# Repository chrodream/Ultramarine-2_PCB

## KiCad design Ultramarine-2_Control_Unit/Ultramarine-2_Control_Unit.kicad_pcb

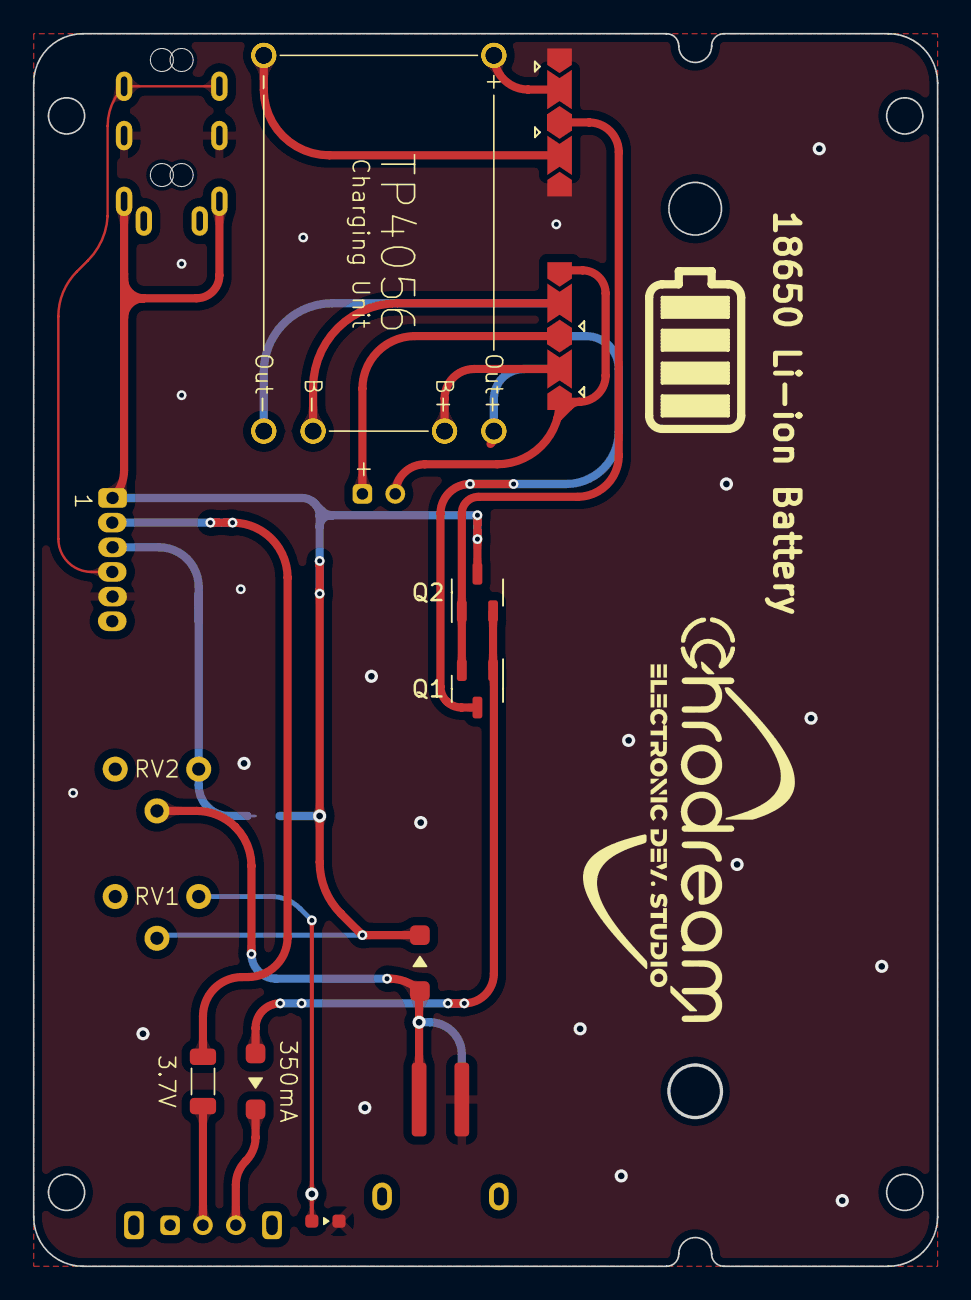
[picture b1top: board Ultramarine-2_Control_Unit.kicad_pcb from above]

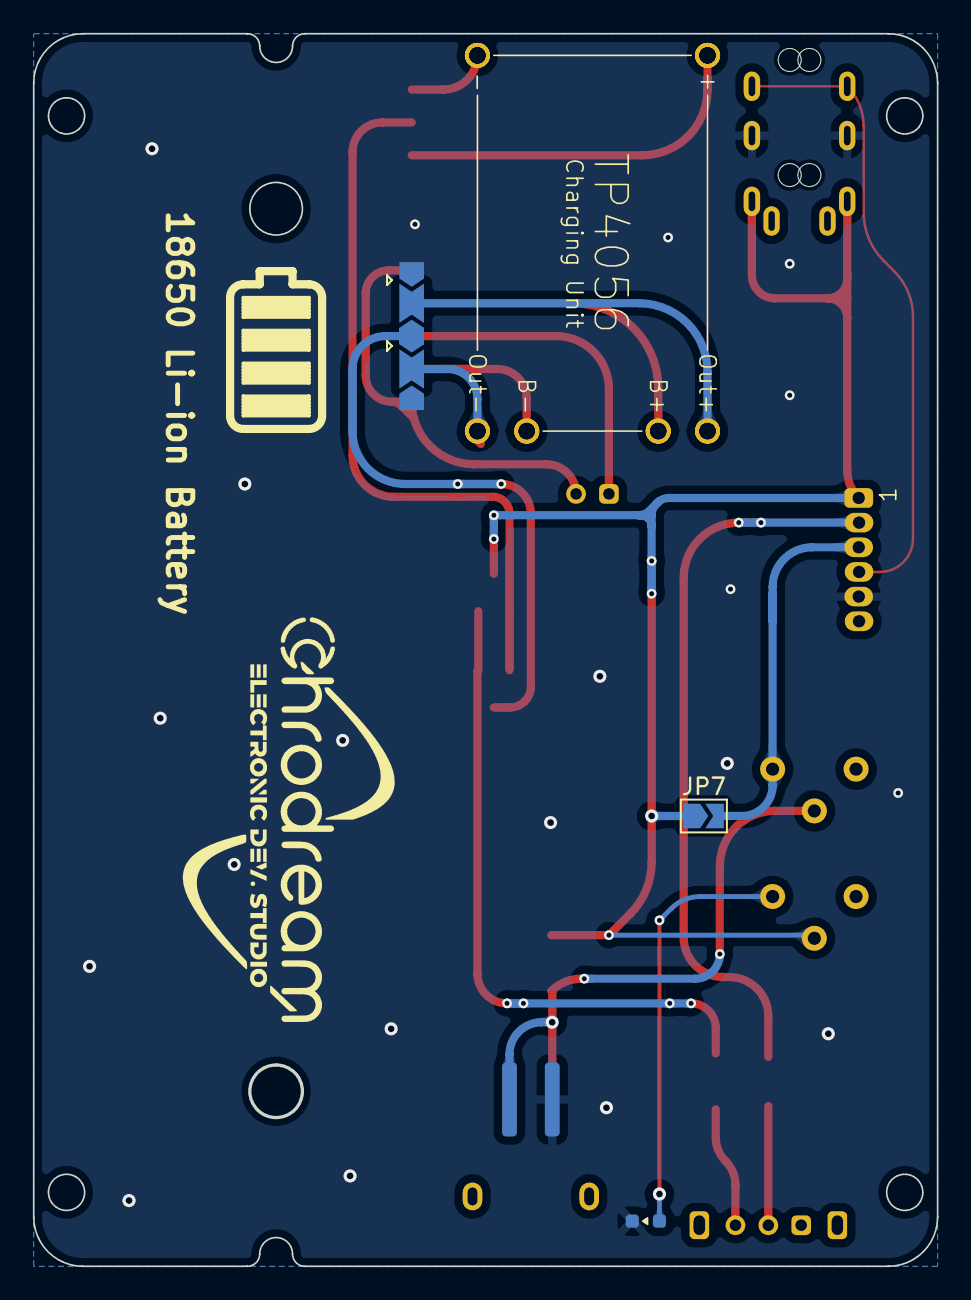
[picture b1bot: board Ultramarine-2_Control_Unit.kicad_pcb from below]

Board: 2 copper layers, 54.9 x 74.9 mm, 22 parts (4 on the bottom side), 20 nets.

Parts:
BT1: LiPo/18650; Battery
BT2: Qi Charging Unit; Micro_USB_Charging
D1: -0.7V; SOD-123
D2: D; SOD-123
D3: Power (WH); LED1608
F1: 350mA; MF-NSMF
J1: Generic_connector; JST_ZH_6
J2: TRRS; MJ-4PP-9
JP1: OUT+ Jumper; Jumper 3pin
JP2: IN+ Jumper; Jumper 3pin
JP3, JP4, JP5, JP6: Jumper 3pin
JP7: Enable_battery_less_mode; SolderJumper-2_P1.3mm_Open_TrianglePad1.0x1.5mm
Q1, Q2: SSM3J332R; SOT-23-3
RV1, RV2: 10K; R_variable
SW1: Slide; SK-12D11VG3
U1, U2: TP4056

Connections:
+5V: D2.1 (K), J1.1, J2.2, JP7.1 (A), Q2.3 (S), RV1.2
/B+: BT1.1 (+), JP1.3 (B), JP3.1 (A)
/B-: BT1.2 (-), JP1.1 (A), JP3.3 (B)
/Bat+: F1.2, J1.2
/Charging: BT2.1 (+), D2.2 (A), RV2.2
/FlexLED: J1.3, JP7.2 (B), RV2.3
/IN+: JP2.3 (B), JP5.1 (A), Q1.2 (G), Q2.1 (D)
/OUT+: JP4.3 (B), JP6.1 (A), Q1.3 (S)
/data: J1.4, J2.4
GND: BT2.2 (-), D3.1 (K), J1.5, J2.3, JP2.1 (A), JP4.1 (A), JP5.3 (B), JP6.3 (B)
unnamed: D1.2 (A), Q1.1 (D), Q2.2 (G)
unnamed: D1.1 (K), SW1.3 (C)
unnamed: D3.2 (A), RV1.3
unnamed: JP1.2 (C), U1.4 (B+), U2.5 (B-)
unnamed: JP2.2 (C), U1.1 (+), U2.2 (-)
unnamed: JP3.2 (C), U1.5 (B-), U2.4 (B+)
unnamed: JP4.2 (C), U1.6 (Out-), U2.3 (Out+)
unnamed: JP5.2 (C), U1.2 (-), U2.1 (+)
unnamed: JP6.2 (C), U1.3 (Out+), U2.6 (Out-)
unnamed: F1.1, SW1.2 (B)

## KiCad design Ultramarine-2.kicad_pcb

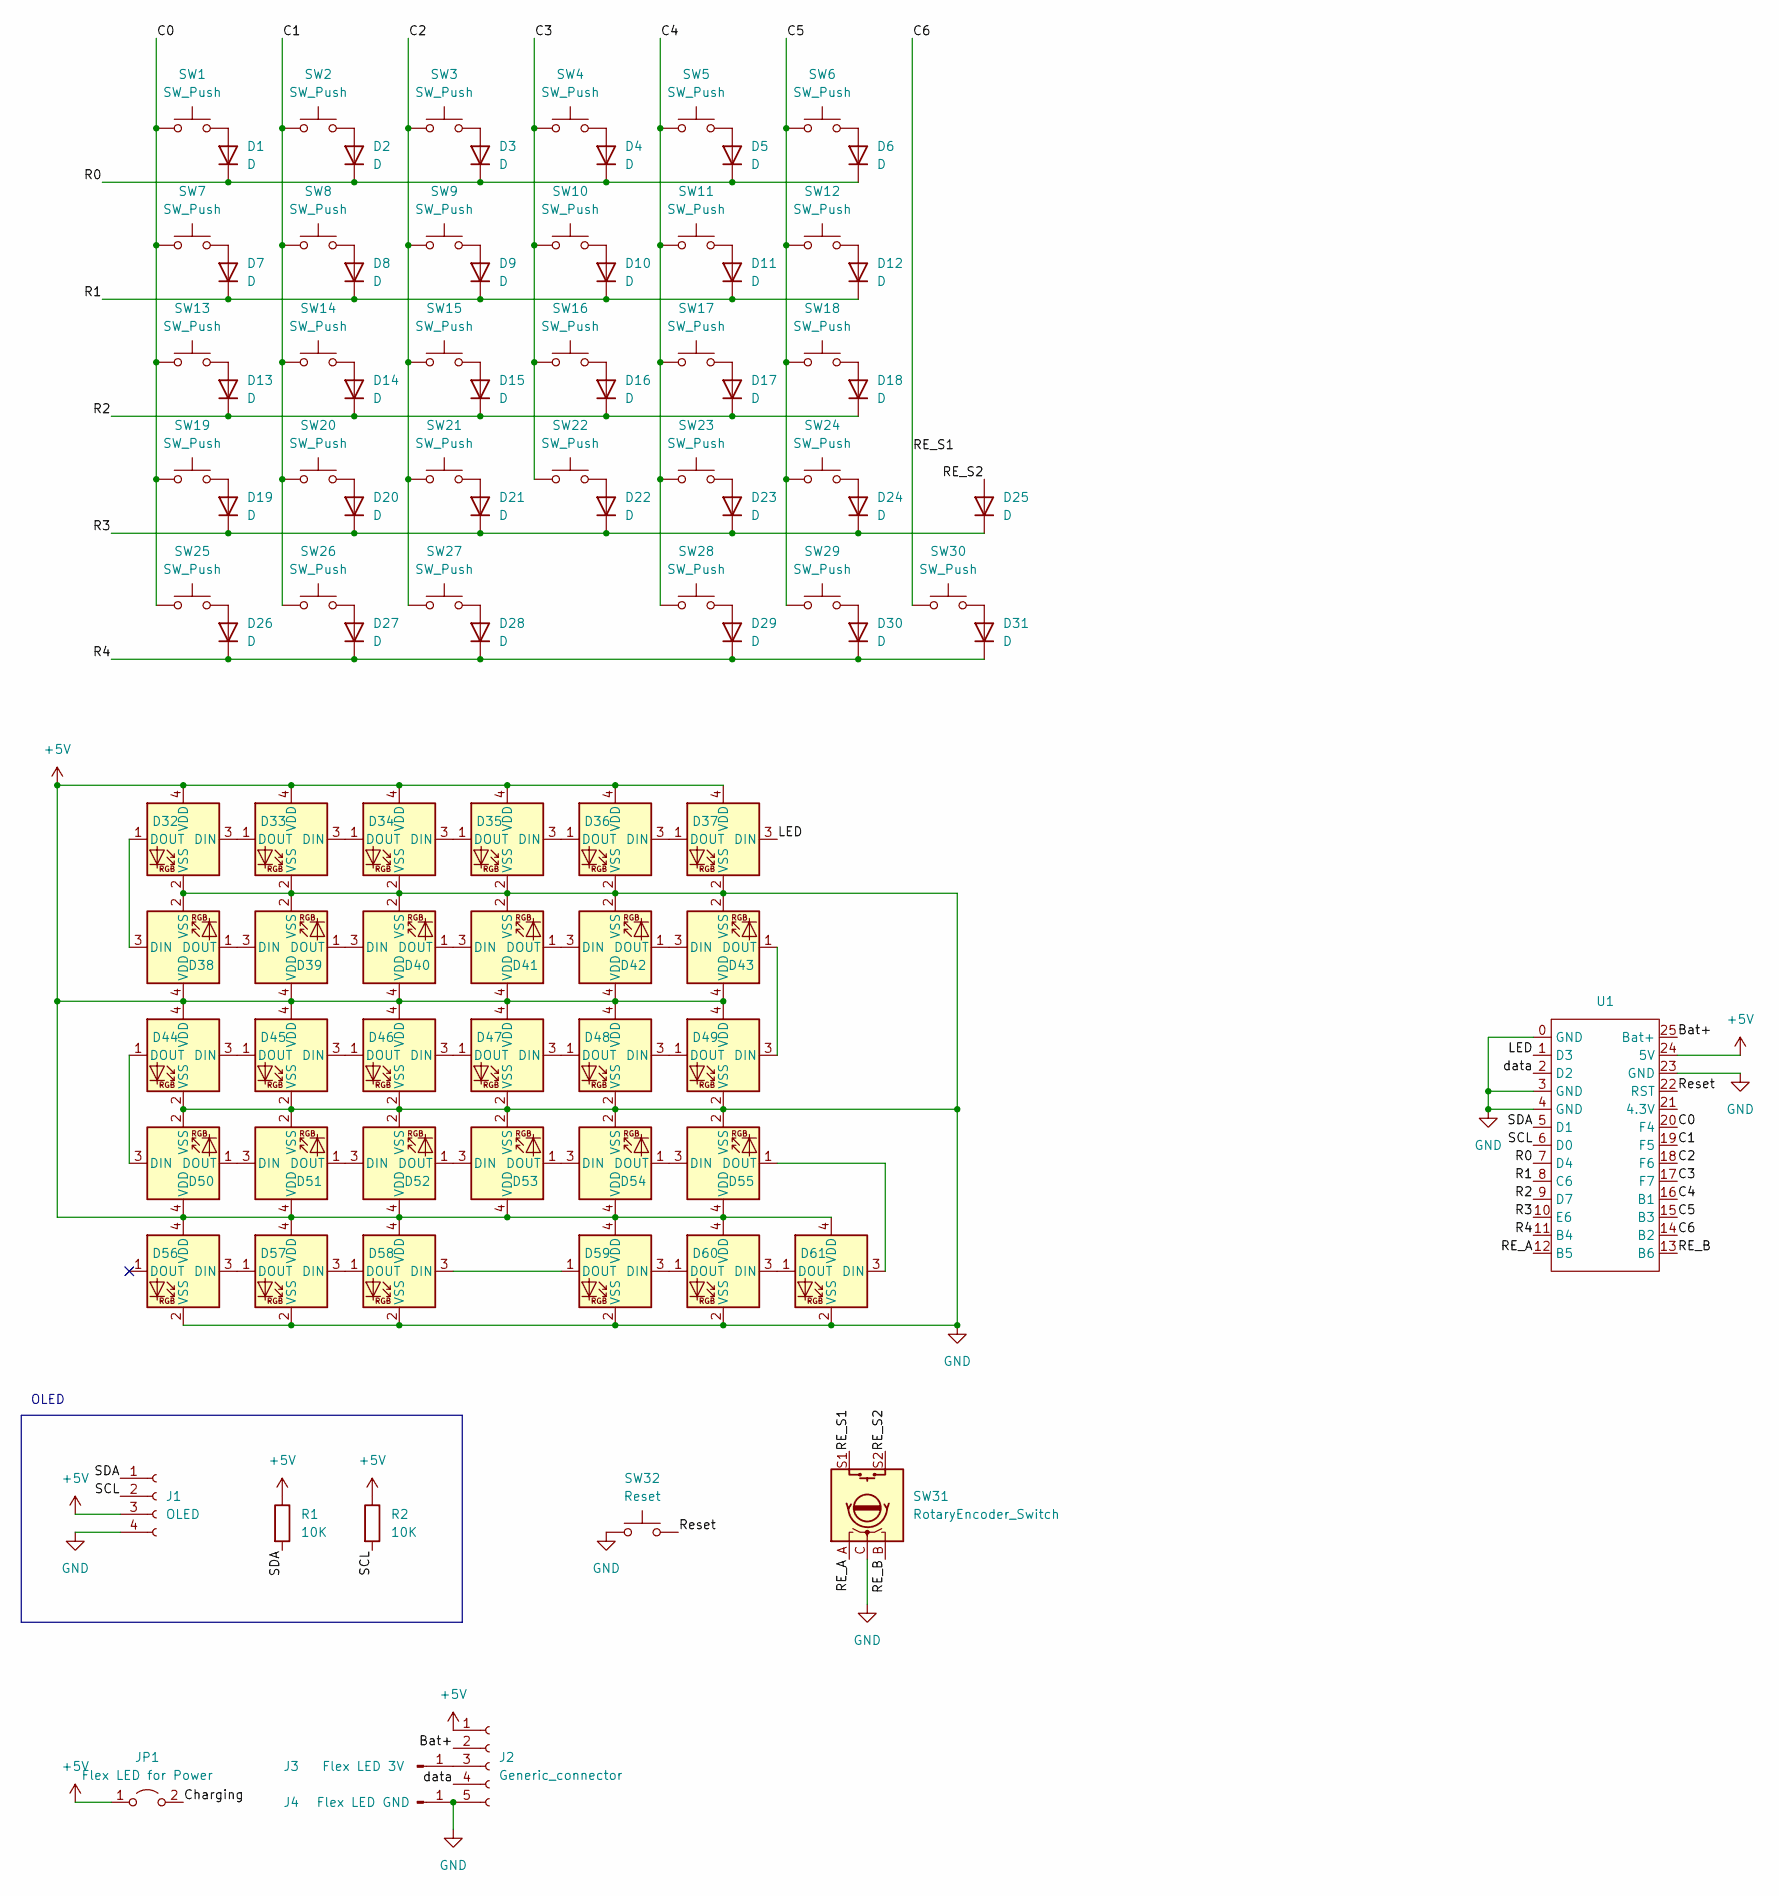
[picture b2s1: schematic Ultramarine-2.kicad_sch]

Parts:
D1, D2, D3, D4, D5, D6, D7, D8, D9, D10, D11, D12, D13, D14, D15, D16, D17, D18, D19, D20, D21, D22, D23, D24, D25, D26, D27, D28, D29, D30, D31: D; SOD-123
D32, D33, D34, D35, D36, D37, D38, D39, D40, D41, D42, D43, D44, D45, D46, D47, D48, D49, D50, D51, D52, D53, D54, D55, D56, D57, D58, D59, D60, D61: SK6812MINI; SK6812-mini
J1: OLED
J2: Generic_connector; PinHeader_1x05_P2.54mm_Horizontal
J3: Flex LED 3V; PTH_Flex_LED
J4: Flex LED GND; PTH_Flex_LED
JP1: Flex LED for Power; SolderJumper-2_P1.3mm_Open_TrianglePad1.0x1.5mm
R1, R2: 10K; R_0603_1608Metric
SW1, SW2, SW3, SW4, SW5, SW6, SW7, SW8, SW9, SW10, SW11, SW12, SW13, SW14, SW15, SW16, SW17, SW18, SW19, SW20, SW21, SW22, SW23, SW24, SW25, SW26, SW27, SW28, SW29, SW30: SW_Push; MX-hotswap
SW31: RotaryEncoder_Switch; EC12
SW32: Reset; Tactlie_Switch
U1: BLE Micro Pro

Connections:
+5V: D32.4 (VDD), D33.4 (VDD), D34.4 (VDD), D35.4 (VDD), D36.4 (VDD), D37.4 (VDD), D38.4 (VDD), D39.4 (VDD), D40.4 (VDD), D41.4 (VDD), D42.4 (VDD), D43.4 (VDD), D44.4 (VDD), D45.4 (VDD), D46.4 (VDD), D47.4 (VDD), D48.4 (VDD), D49.4 (VDD), D50.4 (VDD), D51.4 (VDD), D52.4 (VDD), D53.4 (VDD), D54.4 (VDD), D55.4 (VDD), D56.4 (VDD), D57.4 (VDD), D58.4 (VDD), D59.4 (VDD), D60.4 (VDD), D61.4 (VDD), J1.3, J2.1, JP1.1 (A), R1.1, R2.1, U1.24 (5V)
/Bat+: J2.2, U1.25 (Bat+)
/C0: SW1.2, SW7.2, SW13.2, SW19.2, SW25.2, U1.20 (F4)
/C1: SW2.2, SW8.2, SW14.2, SW20.2, SW26.2, U1.19 (F5)
/C2: SW3.2, SW9.2, SW15.2, SW21.2, SW27.2, U1.18 (F6)
/C3: SW4.2, SW10.2, SW16.2, SW22.2, U1.17 (F7)
/C4: SW5.2, SW11.2, SW17.2, SW23.2, SW28.1, U1.16 (B1)
/C5: SW6.2, SW12.2, SW18.2, SW24.2, SW29.1, U1.15 (B3)
/C6: SW30.1, SW31.S1, U1.14 (B2)
/Charging: JP1.2 (B)
/LED: D37.3 (DIN), U1.1 (D3)
/R0: D1.1 (K), D2.1 (K), D3.1 (K), D4.1 (K), D5.1 (K), D6.1 (K), U1.7 (D4)
/R1: D7.1 (K), D8.1 (K), D9.1 (K), D10.1 (K), D11.1 (K), D12.1 (K), U1.8 (C6)
/R2: D13.1 (K), D14.1 (K), D15.1 (K), D16.1 (K), D17.1 (K), D18.1 (K), U1.9 (D7)
/R3: D19.1 (K), D20.1 (K), D21.1 (K), D22.1 (K), D23.1 (K), D24.1 (K), D25.1 (K), U1.10 (E6)
/R4: D26.1 (K), D27.1 (K), D28.1 (K), D29.1 (K), D30.1 (K), D31.1 (K), U1.11 (B4)
/RE_A: SW31.A, U1.12 (B5)
/RE_B: SW31.B, U1.13 (B6)
/RE_S2: D25.2 (A), SW31.S2
/Reset: SW32.2, U1.22 (RST)
/SCL: J1.2, R2.2, U1.6 (D0)
/SDA: J1.1, R1.2, U1.5 (D1)
/data: J2.4, U1.2 (D2)
GND: D32.2 (VSS), D33.2 (VSS), D34.2 (VSS), D35.2 (VSS), D36.2 (VSS), D37.2 (VSS), D38.2 (VSS), D39.2 (VSS), D40.2 (VSS), D41.2 (VSS), D42.2 (VSS), D43.2 (VSS), D44.2 (VSS), D45.2 (VSS), D46.2 (VSS), D47.2 (VSS), D48.2 (VSS), D49.2 (VSS), D50.2 (VSS), D51.2 (VSS), D52.2 (VSS), D53.2 (VSS), D54.2 (VSS), D55.2 (VSS), D56.2 (VSS), D57.2 (VSS), D58.2 (VSS), D59.2 (VSS), D60.2 (VSS), D61.2 (VSS), J1.4, J2.5, J4.1, SW31.C, SW32.1, U1.0 (GND), U1.3 (GND), U1.4 (GND), U1.23 (GND)
unnamed: D1.2 (A), SW1.1
unnamed: D2.2 (A), SW2.1
unnamed: D3.2 (A), SW3.1
unnamed: D4.2 (A), SW4.1
unnamed: D5.2 (A), SW5.1
unnamed: D6.2 (A), SW6.1
unnamed: D7.2 (A), SW7.1
unnamed: D8.2 (A), SW8.1
unnamed: D9.2 (A), SW9.1
unnamed: D10.2 (A), SW10.1
unnamed: D11.2 (A), SW11.1
unnamed: D12.2 (A), SW12.1
unnamed: D13.2 (A), SW13.1
unnamed: D14.2 (A), SW14.1
unnamed: D15.2 (A), SW15.1
unnamed: D16.2 (A), SW16.1
unnamed: D17.2 (A), SW17.1
unnamed: D18.2 (A), SW18.1
unnamed: D19.2 (A), SW19.1
unnamed: D20.2 (A), SW20.1
unnamed: D21.2 (A), SW21.1
unnamed: D22.2 (A), SW22.1
unnamed: D23.2 (A), SW23.1
unnamed: D24.2 (A), SW24.1
unnamed: D26.2 (A), SW25.1
unnamed: D27.2 (A), SW26.1
unnamed: D28.2 (A), SW27.1
unnamed: D29.2 (A), SW28.2
unnamed: D30.2 (A), SW29.2
unnamed: D31.2 (A), SW30.2
unnamed: D32.3 (DIN), D33.1 (DOUT)
unnamed: D32.1 (DOUT), D38.3 (DIN)
unnamed: D33.3 (DIN), D34.1 (DOUT)
unnamed: D34.3 (DIN), D35.1 (DOUT)
unnamed: D35.3 (DIN), D36.1 (DOUT)
unnamed: D36.3 (DIN), D37.1 (DOUT)
unnamed: D38.1 (DOUT), D39.3 (DIN)
unnamed: D39.1 (DOUT), D40.3 (DIN)
unnamed: D40.1 (DOUT), D41.3 (DIN)
unnamed: D41.1 (DOUT), D42.3 (DIN)
unnamed: D42.1 (DOUT), D43.3 (DIN)
unnamed: D43.1 (DOUT), D49.3 (DIN)
unnamed: D44.3 (DIN), D45.1 (DOUT)
unnamed: D44.1 (DOUT), D50.3 (DIN)
unnamed: D45.3 (DIN), D46.1 (DOUT)
unnamed: D46.3 (DIN), D47.1 (DOUT)
unnamed: D47.3 (DIN), D48.1 (DOUT)
unnamed: D48.3 (DIN), D49.1 (DOUT)
unnamed: D50.1 (DOUT), D51.3 (DIN)
unnamed: D51.1 (DOUT), D52.3 (DIN)
unnamed: D52.1 (DOUT), D53.3 (DIN)
unnamed: D53.1 (DOUT), D54.3 (DIN)
unnamed: D54.1 (DOUT), D55.3 (DIN)
unnamed: D55.1 (DOUT), D61.3 (DIN)
unnamed: D56.3 (DIN), D57.1 (DOUT)
unnamed: D57.3 (DIN), D58.1 (DOUT)
unnamed: D58.3 (DIN), D59.1 (DOUT)
unnamed: D59.3 (DIN), D60.1 (DOUT)
unnamed: D60.3 (DIN), D61.1 (DOUT)
unnamed 83: J2.3, J3.1; also elsewhere on the board

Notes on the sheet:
OLED

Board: 2 copper layers, 101 parts (64 on the bottom side), 83 nets, no tracks yet.

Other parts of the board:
Je: Flex LED 3V; PTH_Flex_LED

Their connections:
unnamed 83: Je.1; also elsewhere on the board

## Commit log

2023-06-22 add PCB dxf file
2023-06-29 Added Qi charging unit
2023-06-30 add battery charging unit's footprint
2023-07-04 add PCB patterns
2023-07-05 wiring +5V
2023-07-09 make left hand type
2023-08-05 starts build left hand
2023-08-24 reversible type
2023-10-09 Changed to 6pin connector
2023-12-17 completed version
